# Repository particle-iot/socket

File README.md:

The Spark Socket
=====

These are the design files for the Spark Socket, developed by Hex Labs, Inc. dba Spark Devices.

These files have been made available online through a [Creative Commons Attribution-ShareAlike 3.0](http://creativecommons.org/licenses/by-sa/3.0/) license.

You are welcome to distribute, remix, and use these files for commercial purposes. If you do so, please attribute the original design to Spark Devices both on the website and on the physical packaging of the product or in the instruction manual. All derivative works must be published under the same or a similar license.

## WARNING: High voltage

If you choose to use these design files, please be forewarned: working with high voltage designs, especially non-isolated ones, can be extremely dangerous. Please proceed with extreme caution. We cannot guarantee the safety of these designs, as they had not yet been put through certification. If you download these files, you are taking upon yourself any liability for injury or property damage.

## The Story

Development of the Spark Socket began in December, 2011, sparked (sorry) by Zach's experiences with his deaf father. Over the next eleven months, Spark went from an idea to a product. On November 13, 2012, the Spark Socket was published on the crowdfunding platform Kickstarter. The Kickstarter campaign site can be found [here](http://www.kickstarter.com/projects/sparkdevices/spark-upgrade-your-lights-with-wi-fi-and-apps).

The Spark Socket Kickstarter campaign ran from November 13, 2012 to December 13, 2012. In that time, roughly 1,600 individuals devoted their time and money to supporting Spark with a total of $125,588 pledged. The funding threshold, however, for the campaign was $250,000. Because that threshold was not reached by the end of the campaign, the campaign closed unsuccessfully, and no credit cards were charged.

The Spark team continued to work on the Spark Socket after the close of the campaign, taking pre-orders on [their website](http://www.sparkdevices.com) . Between December 13, 2012 and March 25, 2013, orders for ~1,800 Spark Sockets were placed; many were from previous Kickstarter backers, and many more were from newcomers.

On March 25, 2013, the Spark team announced that they would be discontinuing development work on the Spark Socket. The design files for the product were released here on github for others to use and learn from.

## What's Included

This distro contains two versions of the Spark Socket, named Version 1 and Version 2.

Version 1 of the Spark Socket is the version that was showcased in our Kickstarter video. The design includes four circuit boards, wrapped in a cuboid shape around the inner core of the plastic enclosure.

As development on the Socket continued, Version 2 of the Spark Socket was created. Version 2 re-oriented the design so that there are only two circuit boards: one with the high voltage components of the circuit, the other with the low voltage components of the circuit. This design made integrating the power supply much easier, and would be significantly easier to assemble. It also had enough empty space that the plastic enclosure could theoretically be made smaller, although development efforts stopped before the outer enclosure was changed.

## Basic structure

The design of the Spark Socket includes four major subsystems:

- **Power supply**. The Socket sources the power for its circuitry directly from the high-voltage AC line to which it is attached. Although this may be possible with an isolated switch-mode power supply, we chose a non-isolated design to save on the bill of materials and to save space. The power supply must be able to source at least 300mA of current (mostly for the transmit events of the Wi-Fi module), although the average power draw should be closer to 50mA.
- **Micro-controller**. Because the Spark Socket was originally built using an Arduino, the micro-controller we are using is an Atmel ATmega328p. This is a low-cost 8-bit micro-controller that is very easy to develop for. For encrypted communications, a 32-bit micro-controller (such as an STM32 Cortex M3) may be used instead.
- **Wi-Fi module**. For the Socket prototype, we used a Roving Networks RN-171 Wi-Fi module. These modules are great because they are very easy to work with and get up and running quickly. They are, however, quite expensive; even with high volumes, the order price was greater than $15. Spark will be using the Texas Instruments CC3000 Wi-Fi module in our other projects, which is smaller, lower cost, and has a simpler set-up process. We recommend the CC3000 for ongoing development work.
- **TRIAC Dimmer**. The most tried-and-true way to dim a light bulb is using a TRIAC. A zero-cross detector informs the micro-controller of the timing of the AC current, and the TRIAC dimmer is activated at a specificied time interval after the zero-cross, based on the chosen dim level. TRIAC dimmers work best with resistive loads (such as incandescent bulbs), and will also work with CFLs that are labeled "dimmable" as well as LED bulbs that are labeled "dimmable". TRIAC dimmers are also called "leading edge" dimmers.

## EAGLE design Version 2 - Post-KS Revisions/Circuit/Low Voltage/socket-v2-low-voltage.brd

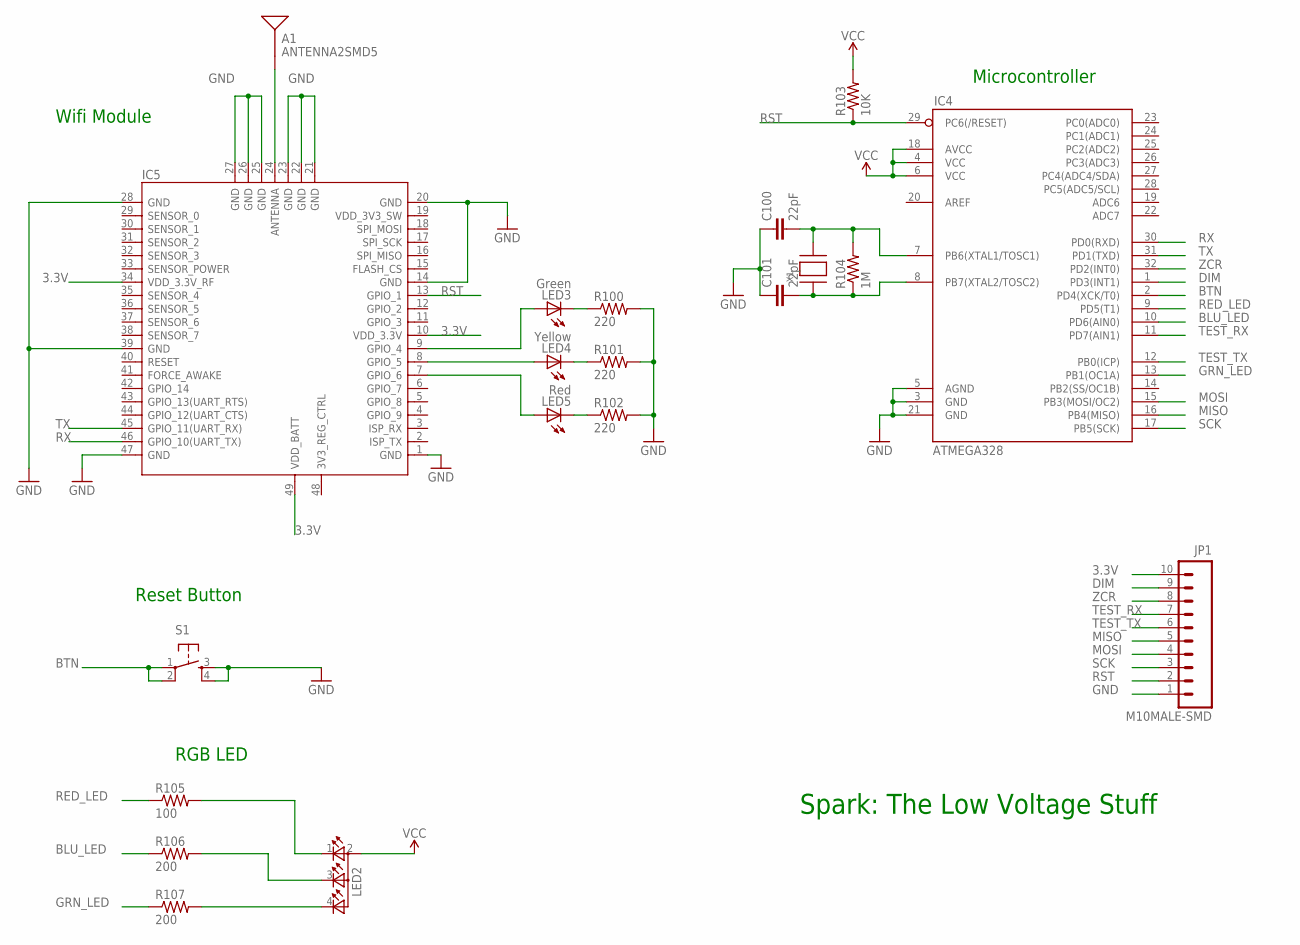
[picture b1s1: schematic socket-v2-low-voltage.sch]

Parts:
A1: ANTENNA2SMD5; ANTENNA-CHIP5
C100, C101: 22pF; 0603-CAP
IC4: ATMEGA328; TQFP32-08
IC5: WIFI-RN-171; 49P-1.27-26.67X17.78
JP1: M10MALE-SMD; 1X10-2MM-MALE-SMD
LED2: TOPLED-3PLCC; P-LCC-4-3
LED3: Green; LED-0603
LED4: Yellow; LED-0603
LED5: Red; LED-0603
R100, R101, R102: 220; 0603-RES
R103: 10K; 0603-RES
R104: 1M; 0603-RES
R105: 100; 0603-RES
R106, R107: 200; 0603-RES
S1: TAC_SWITCHSMD; TACTILE_SWITCH_SMD
X1: XTALNX5032; NX5032

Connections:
3.3V: IC4.4 (VCC), IC4.6 (VCC), IC4.18 (AVCC), IC5.10 (VDD_3.3V), IC5.34 (VDD_3.3V_RF), IC5.49 (VDD_BATT), JP1.10, LED2.2 (A2), R103.2
BLU_LED: IC4.10 (PD6(AIN0)), R106.1
BTN: IC4.2 (PD4(XCK/T0)), S1.1, S1.2
DIM: IC4.1 (PD3(INT1)), JP1.9
GND: C100.1, C101.1, IC4.3 (GND), IC4.5 (AGND), IC4.21 (GND), IC5.1 (GND), IC5.14 (GND), IC5.20 (GND), IC5.21 (GND), IC5.22 (GND), IC5.23 (GND), IC5.25 (GND), IC5.26 (GND), IC5.27 (GND), IC5.28 (GND), IC5.39 (GND), IC5.47 (GND), JP1.1, R100.2, R101.2, R102.2, S1.3, S1.4
GRN_LED: IC4.13 (PB1(OC1A)), R107.1
MISO: IC4.16 (PB4(MISO)), JP1.5
MOSI: IC4.15 (PB3(MOSI/OC2)), JP1.4
unnamed: LED2.1 (CRED), R105.2
unnamed: LED2.4 (CGREEN), R107.2
unnamed: LED2.3 (CBLUE), R106.2
unnamed: IC5.9 (GPIO_4), LED3.A
unnamed: LED3.C, R100.1
unnamed: LED4.C, R101.1
unnamed: LED5.C, R102.1
unnamed: IC5.8 (GPIO_5), LED4.A
unnamed: IC5.7 (GPIO_6), LED5.A
unnamed: A1.FEED, IC5.24 (ANTENNA)
unnamed: C100.2, IC4.7 (PB6(XTAL1/TOSC1)), R104.2, X1.P$2
RED_LED: IC4.9 (PD5(T1)), R105.1
RST: IC4.29 (PC6(/RESET)), IC5.13 (GPIO_1), JP1.2, R103.1
RX: IC4.30 (PD0(RXD)), IC5.46 (GPIO_10(UART_TX))
SCK: IC4.17 (PB5(SCK)), JP1.3
TEST_RX: IC4.11 (PD7(AIN1)), JP1.7
TEST_TX: IC4.12 (PB0(ICP)), JP1.6
TX: IC4.31 (PD1(TXD)), IC5.45 (GPIO_11(UART_RX))
XTAL1: C101.2, IC4.8 (PB7(XTAL2/TOSC2)), R104.1, X1.P$1
ZCR: IC4.32 (PD2(INT0)), JP1.8

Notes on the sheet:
Wifi Module
Reset Button
RGB LED
Microcontroller
Spark: The Low Voltage Stuff

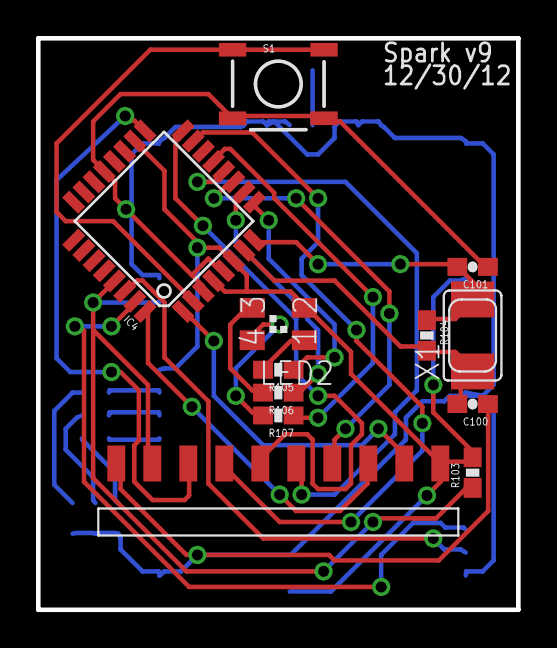
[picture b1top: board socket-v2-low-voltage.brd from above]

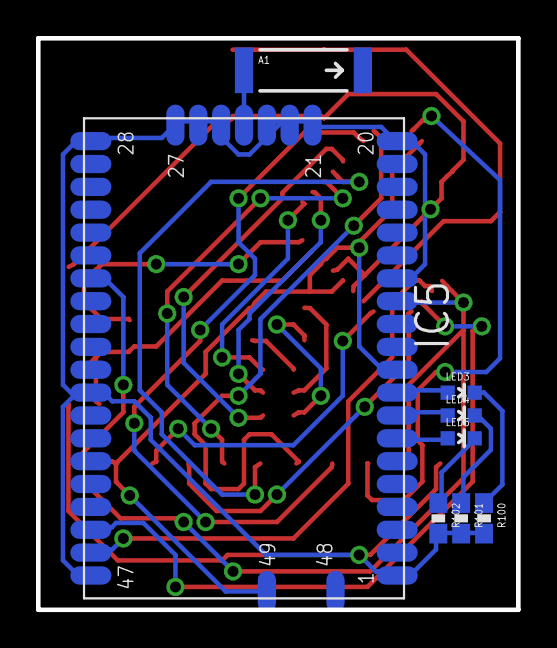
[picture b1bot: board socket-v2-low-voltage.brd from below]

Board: 2 copper layers, 26.7 x 31.8 mm, 20 parts (8 on the bottom side), 28 nets.

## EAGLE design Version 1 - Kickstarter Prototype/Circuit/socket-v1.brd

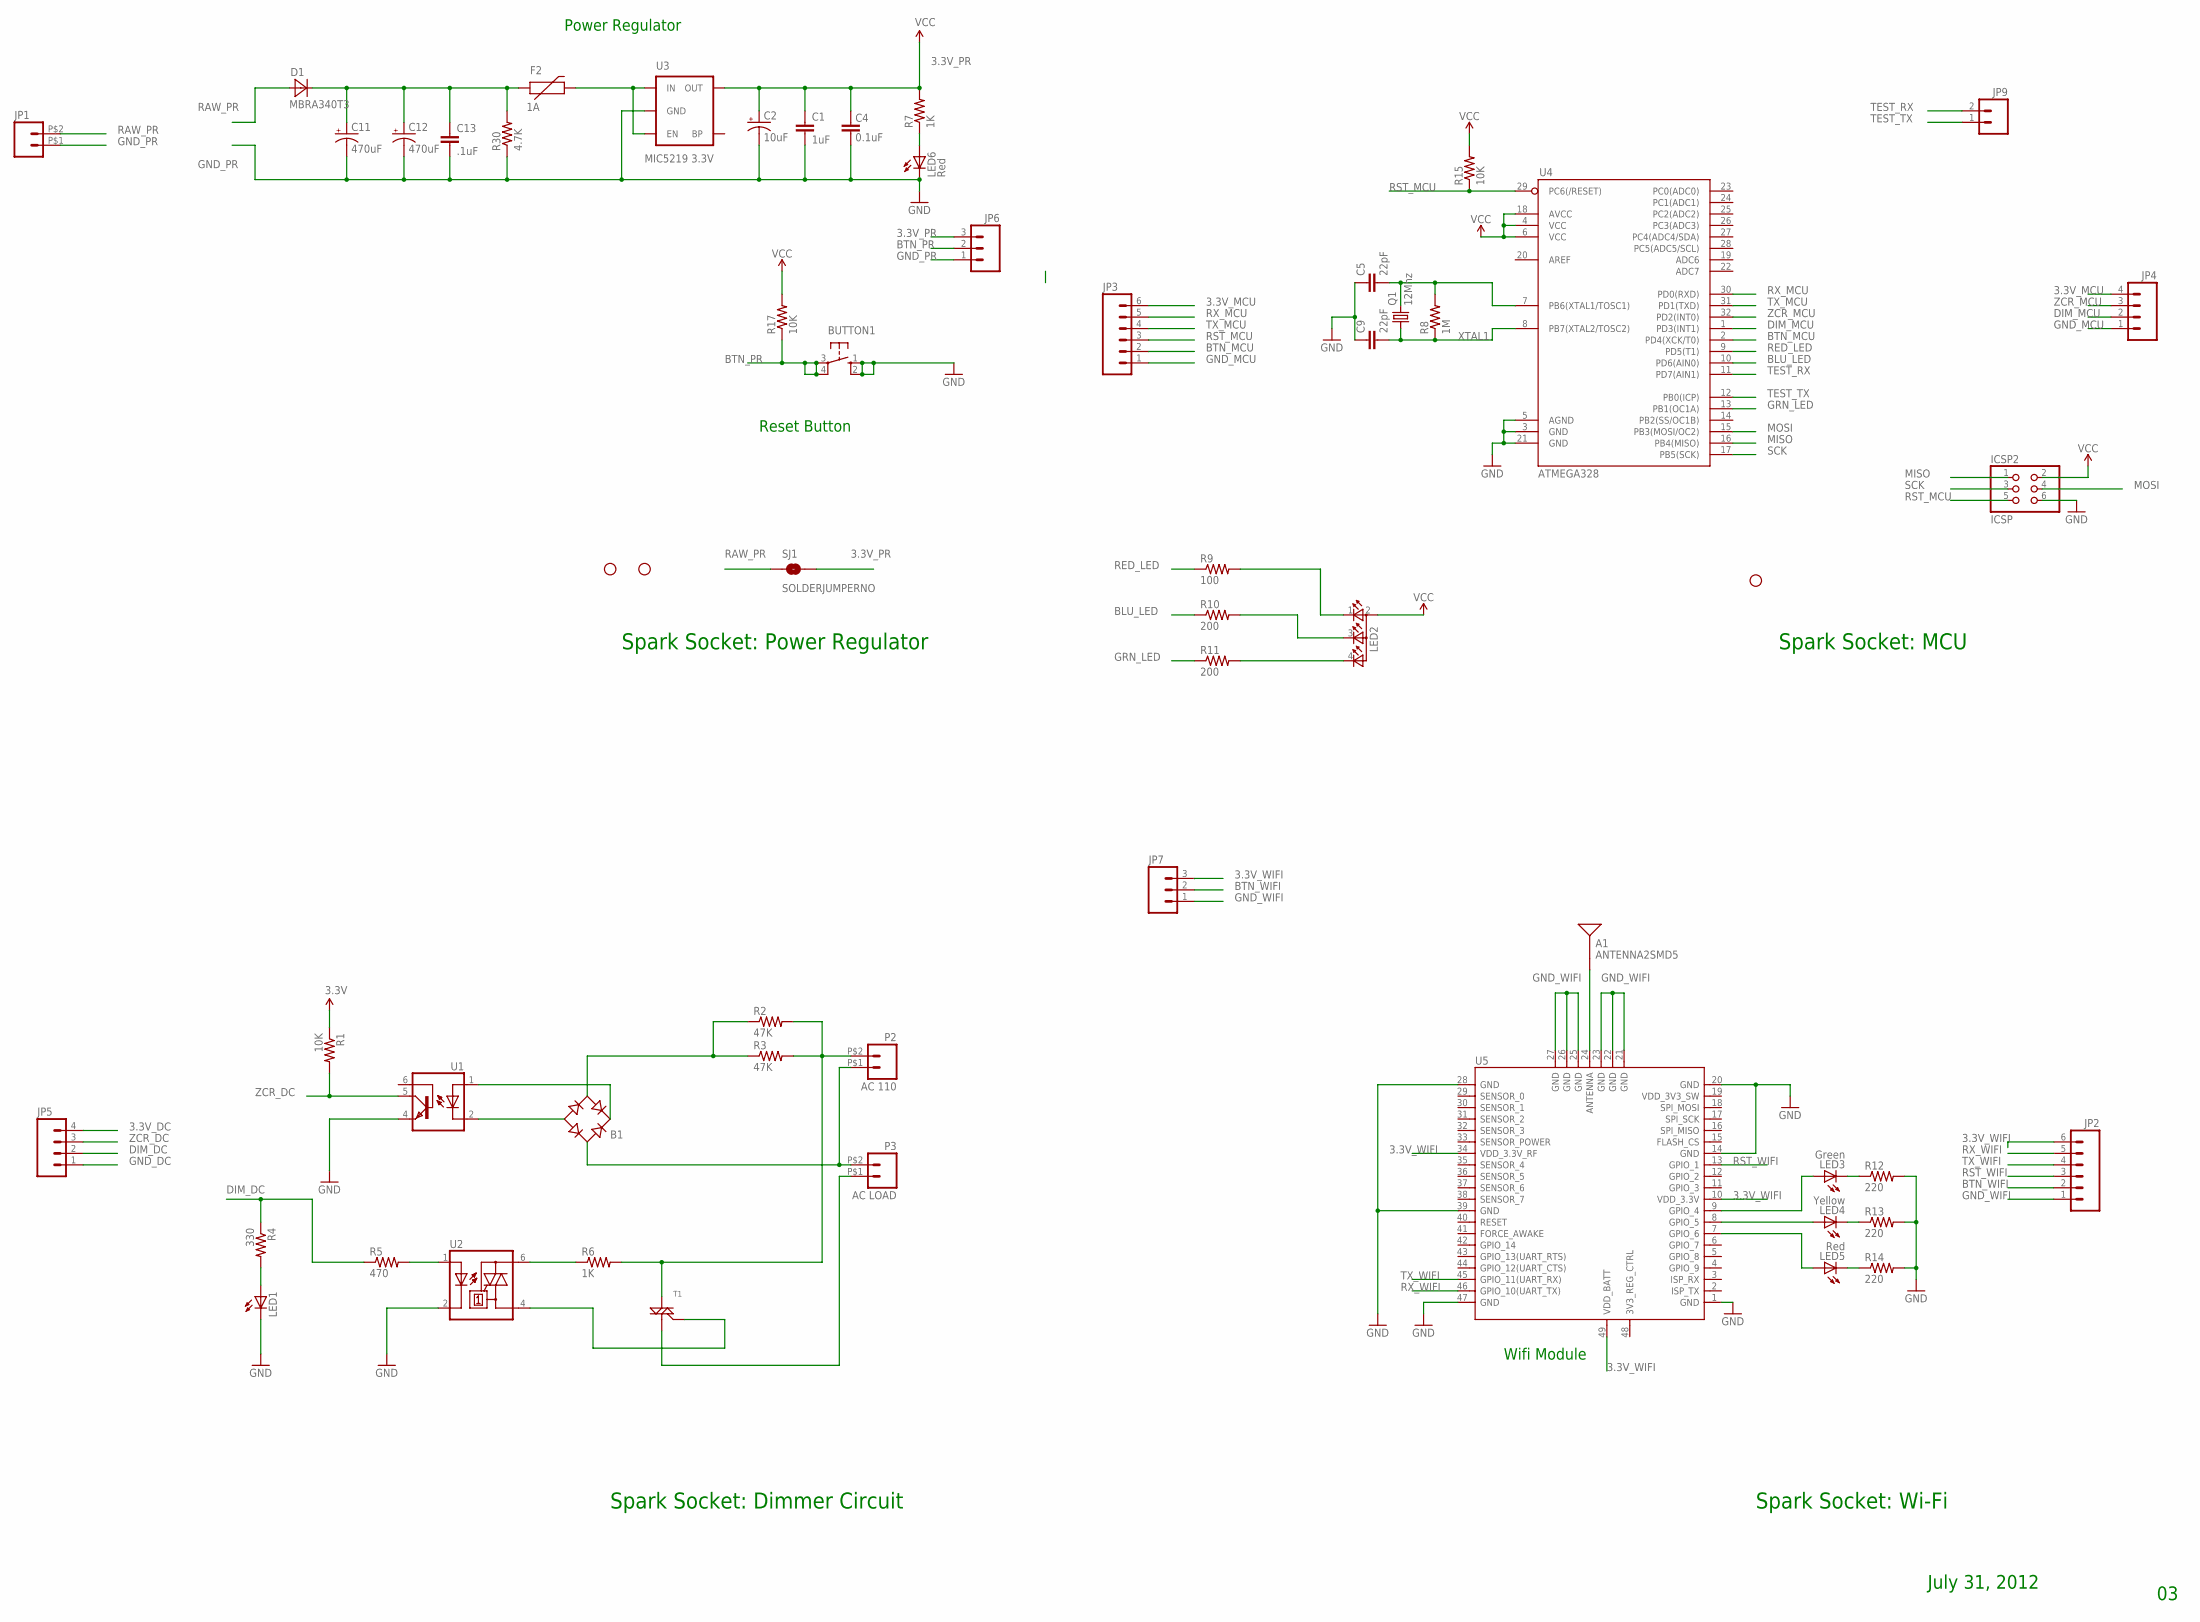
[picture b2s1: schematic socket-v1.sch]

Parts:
A1: ANTENNA2SMD5; ANTENNA-CHIP5
B1: DF10S; DFS
BUTTON1: 10-XX; B3F-10XX
C1: 1uF; 0603-CAP
C2: 10uF; EIA3216
C4: 0.1uF; 0603-CAP
C5, C9: 22pF; 0603-CAP
C11, C12: 470uF; EIA3216
C13: .1uF; 1206
D1: MBRA340T3; SMA
F2: 1A; PTC-1206
ICSP2: ICSP; 2X03
JP1: M02PTH2; 1X02_BIG
JP2, JP3: M06SIP; 1X06
JP4, JP5: M04PTH; 1X04
JP6, JP7: M03PTH; 1X03
JP8, JP10, JP11: STAND-OFF
JP9: M02PTH; 1X02
LED1: LED0603; LED-0603
LED2: TOPLED-3PLCC; P-LCC-4-3
LED3: Green; LED-0603
LED4: Yellow; LED-0603
LED5, LED6: Red; LED-0603
P2: AC 110; 1X02_BIG
P3: AC LOAD; 1X02_BIG
Q1: 12Mhz; HC49UP
R1, R15, R17: 10K; 0603-RES
R2, R3: 47K; 1206
R4: 330; 0603-RES
R5: 470; 0603-RES
R6: 1K; 1206
R7: 1K; 0603-RES
R8: 1M; 0603-RES
R9: 100; 0603-RES
R10, R11: 200; 0603-RES
R12, R13, R14: 220; 0603-RES
R30: 4.7K; 0603-RES
SJ1: SOLDERJUMPERNO; SJ_2S-NO
T1: TRIACSMD; SOT223
U1: 4N25SM; DIL6-SMD; MPN 4N25SM
U2: MOC3031S; DIL6-SMD; MPN MOC3031SM
U3: MIC5219 3.3V; SOT23-5
U4: ATMEGA328; TQFP32-08
U5: WIFI-RN-171; 49P-1.27-26.67X17.78

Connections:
3.3V_DC: JP5.4, R1.1
3.3V_MCU: ICSP2.2, JP3.6, JP4.4, LED2.2 (A2), R15.2, U4.4 (VCC), U4.6 (VCC), U4.18 (AVCC)
3.3V_PR: C1.1, C2.A (+), C4.2, JP6.3, R7.2, R17.2, SJ1.2, U3.5 (OUT)
3.3V_WIFI: JP2.6, JP7.3, U5.10 (VDD_3.3V), U5.34 (VDD_3.3V_RF), U5.49 (VDD_BATT)
ASDF: C11.A (+), C12.A (+), C13.1, D1.C, F2.1, R30.2
BLU_LED: R10.1, U4.10 (PD6(AIN0))
BTN_MCU: JP3.2, U4.2 (PD4(XCK/T0))
BTN_PR: BUTTON1.3, BUTTON1.4 (P1), JP6.2, R17.1
BTN_WIFI: JP2.2, JP7.2
DIM_DC: JP5.2, R4.1, R5.1
DIM_MCU: JP4.2, U4.1 (PD3(INT1))
GND_DC: JP5.1, LED1.C, U1.4 (EMI), U2.2 (C)
GND_MCU: C5.1, C9.1, ICSP2.6, JP3.1, JP4.1, U4.3 (GND), U4.5 (AGND), U4.21 (GND)
GND_PR: BUTTON1.1 (S), BUTTON1.2 (S1), C1.2, C2.C (-), C4.1, C11.C (-), C12.C (-), C13.2, JP1.P$1 (1), JP6.1, LED6.C, R30.1, U3.2 (GND)
GND_WIFI: JP2.1, JP7.1, R12.2, R13.2, R14.2, U5.1 (GND), U5.14 (GND), U5.20 (GND), U5.21 (GND), U5.22 (GND), U5.23 (GND), U5.25 (GND), U5.26 (GND), U5.27 (GND), U5.28 (GND), U5.39 (GND), U5.47 (GND)
GRN_LED: R11.1, U4.13 (PB1(OC1A))
MISO: ICSP2.1, U4.16 (PB4(MISO))
MOSI: ICSP2.4, U4.15 (PB3(MOSI/OC2))
unnamed: LED2.1 (CRED), R9.2
unnamed: LED6.A, R7.1
unnamed: F2.2, U3.1 (IN), U3.3 (EN)
unnamed: B1.-, U1.2 (C)
unnamed: B1.+, U1.1 (A)
unnamed: B1.AC2, R2.1, R3.1
unnamed: P2.P$2 (2), R2.2, R3.2, R6.2, T1.2 (M2)
unnamed: LED2.4 (CGREEN), R11.2
unnamed: R6.1, U2.6 (A2)
unnamed: T1.3 (G), U2.4 (A1)
unnamed: P3.P$1 (1), T1.1 (M1)
unnamed: B1.AC1, P2.P$1 (1), P3.P$2 (2)
unnamed: LED1.A, R4.2
unnamed: LED2.3 (CBLUE), R10.2
unnamed: R5.2, U2.1 (A)
unnamed: LED3.A, U5.9 (GPIO_4)
unnamed: LED3.C, R12.1
unnamed: LED4.C, R13.1
unnamed: LED5.C, R14.1
unnamed: LED4.A, U5.8 (GPIO_5)
unnamed: LED5.A, U5.7 (GPIO_6)
unnamed: A1.FEED, U5.24 (ANTENNA)
unnamed: C5.2, Q1.2, R8.2, U4.7 (PB6(XTAL1/TOSC1))
RAW_PR: D1.A, JP1.P$2 (2), SJ1.1
RED_LED: R9.1, U4.9 (PD5(T1))
RST_MCU: ICSP2.5, JP3.3, R15.1, U4.29 (PC6(/RESET))
RST_WIFI: JP2.3, U5.13 (GPIO_1)
RX_MCU: JP3.5, U4.30 (PD0(RXD))
RX_WIFI: JP2.5, U5.46 (GPIO_10(UART_TX))
SCK: ICSP2.3, U4.17 (PB5(SCK))
TEST_RX: JP9.2, U4.11 (PD7(AIN1))
TEST_TX: JP9.1, U4.12 (PB0(ICP))
TX_MCU: JP3.4, U4.31 (PD1(TXD))
TX_WIFI: JP2.4, U5.45 (GPIO_11(UART_RX))
XTAL1: C9.2, Q1.1, R8.1, U4.8 (PB7(XTAL2/TOSC2))
ZCR_DC: JP5.3, R1.2, U1.5 (COL)
ZCR_MCU: JP4.3, U4.32 (PD2(INT0))

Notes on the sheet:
Spark Socket: Wi-Fi
July 31, 2012
Spark Socket: MCU
Spark Socket: Power Regulator
Spark Socket: Dimmer Circuit
Power Regulator
Wifi Module
Reset Button

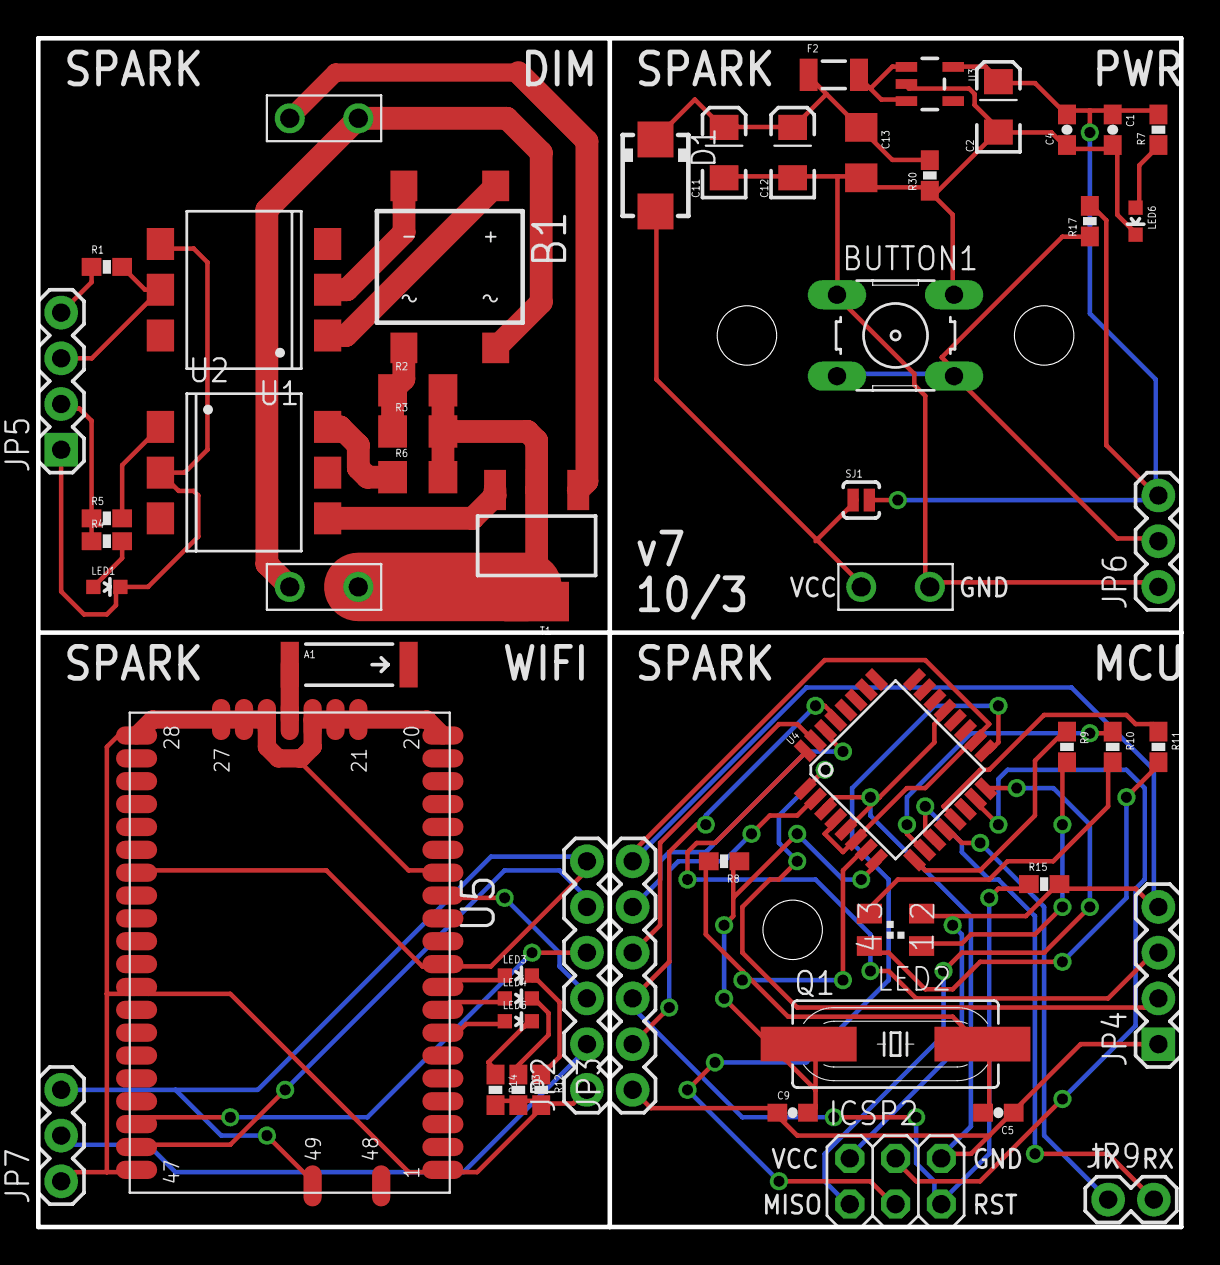
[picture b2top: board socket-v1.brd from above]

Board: 2 copper layers, 63.5 x 66.0 mm, 58 parts (0 on the bottom side), 55 nets.

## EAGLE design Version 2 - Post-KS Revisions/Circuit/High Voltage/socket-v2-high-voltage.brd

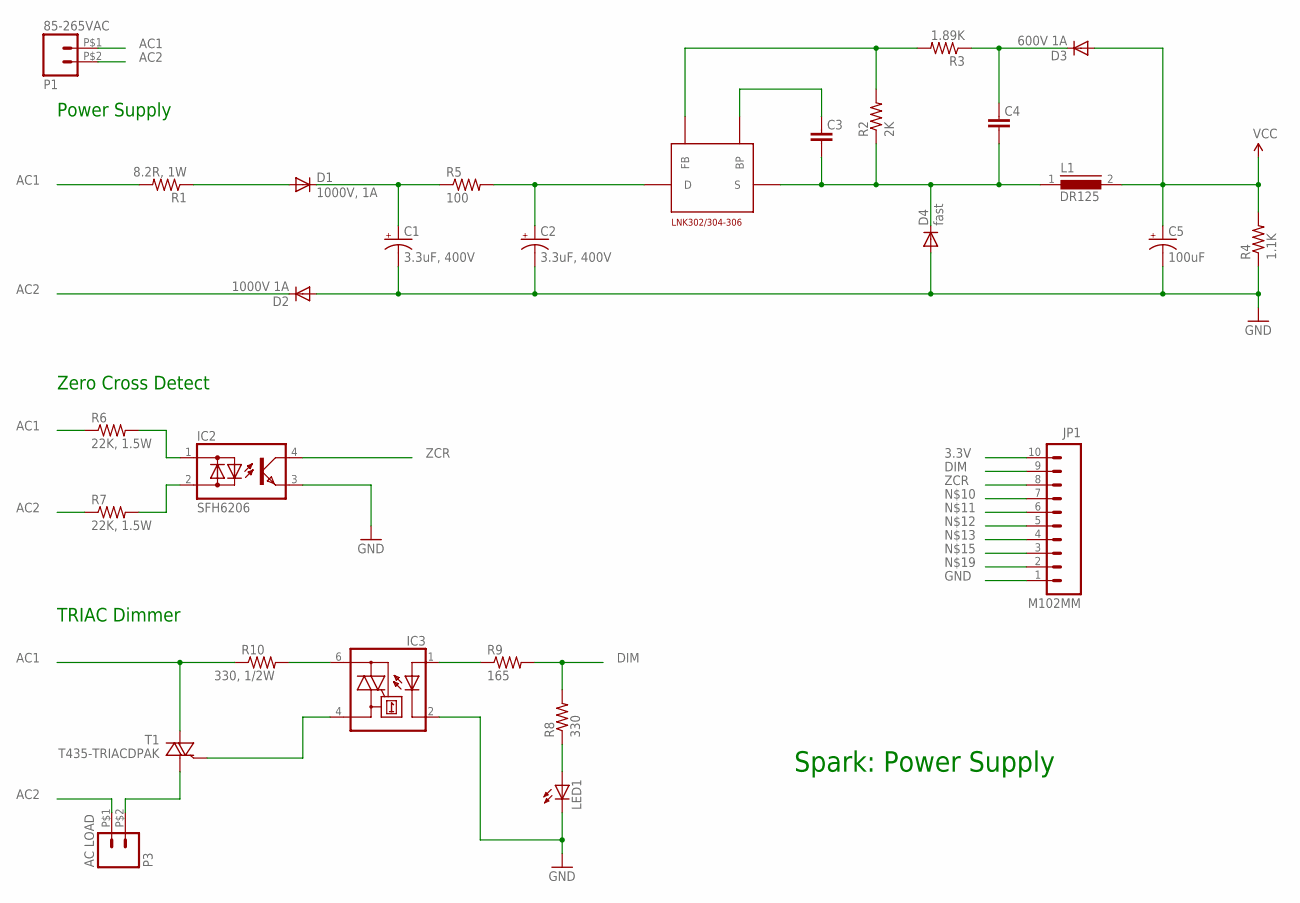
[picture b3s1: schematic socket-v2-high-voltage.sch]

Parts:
C1, C2: 3.3uF, 400V; E3,5-8
C3: 0.1uF; 0603-CAP
C4: 10uF, 50V; 0805
C5: 100uF; EIA3528
D1: 1000V, 1A; SMA-DIODE
D2: 1000V 1A; SMA-DIODE
D3: 600V 1A; SMA-DIODE
D4: fast; SMA-DIODE
IC1: LNK302/304-306; SMD-8B
IC2: SFH6206; DIL4-SMD
IC3: MOC3031S; DIL6-SMD; MPN MOC3031SM
JP1: M102MM; 1X10-2MM
L1: DR125
LED1: LED0603; LED-0603
P1: 85-265VAC; 1X02_BIG
P3: AC LOAD; 1X02_BIG
R1: 8.2R, 1W; 0207/10
R2: 2K; 0805
R3: 1.89K; 0805
R4: 1.1K; 0603-RES
R5: 100; 0204/7
R6, R7: 22K, 1.5W; R2512
R8: 330; 0805
R9: 165; 0805
R10: 330, 1/2W; R1210
T1: T435-TRIACDPAK; TO252

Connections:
3.3V: C5.A (+), D3.A, JP1.10, L1.2, R4.2
$N$100: C3.1, C4.1, D4.C, IC1.S1 (S), L1.1, R2.1
$N$101: C2.+, IC1.D, R5.2
AC1: P1.P$1 (1), R1.2, R6.1, R10.1, T1.2 (A2)
AC2: D2.C, P1.P$2 (2), P3.P$1 (1), R7.1
DIM: JP1.9, R8.2, R9.2
GND: C1.-, C2.-, C5.C (-), D2.A, D4.A, IC2.3 (E), IC3.2 (C), JP1.1, LED1.C, R4.1
unnamed: C4.2, D3.C, R3.1
unnamed: C3.2, IC1.BP
unnamed: IC3.1 (A), R9.1
unnamed: IC3.6 (A2), R10.2
unnamed: IC3.4 (A1), T1.3 (G)
unnamed: P3.P$2 (2), T1.1 (A1)
unnamed: IC2.1 (AC1), R6.2
unnamed: LED1.A, R8.1
unnamed: C1.+, D1.C, R5.1
unnamed: IC1.FB, R2.2, R3.2
unnamed: IC2.2 (AC2), R7.2
RAW_PR: D1.A, R1.1
ZCR: IC2.4 (C), JP1.8

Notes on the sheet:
Power Supply
Spark: Power Supply
Zero Cross Detect
TRIAC Dimmer

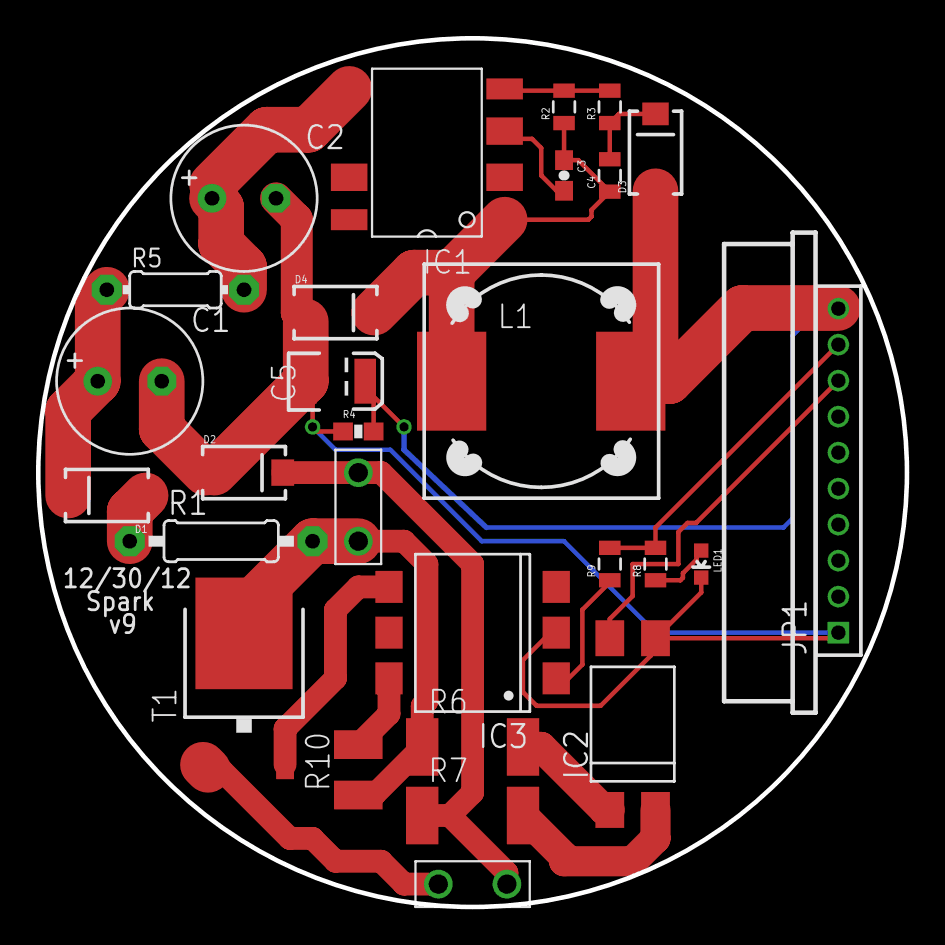
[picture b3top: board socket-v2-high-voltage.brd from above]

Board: 2 copper layers, 48.3 x 48.3 mm, 28 parts (0 on the bottom side), 20 nets.

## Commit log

2013-03-25 Added files and updated README
2013-03-25 Cleaned up filenames and added latest files
2013-03-25 Removed deleted files
2013-03-25 Added warning label to README
2025-08-20 Add CC-BY-SA license

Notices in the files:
parts and their libraries:
SparkFun: Licensing: CC v3.0 Share-Alike You are welcome to use this library for commercial purposes.
